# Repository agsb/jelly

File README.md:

-- THIS FILE IS A STUB ---

_01/05/2024 I'm on vacancy for refresh some ideas_

_22/03/2026 Review for make it_

# Jelly revision 2.0

Jelly is a concept, a alternative computer with a diferent paradigm, not for performance but for design.

Jelly is a minimal DIY 8-bit CPU made with CMOS chips, to perform computations using sequential access tapes.

## What is it ?

How make a new cpu without memory address, using only sequential access, for code, data and input/output ?

I want to learn about how old cpus are made by inside and understand about signals, gates, latches, pipelines, etc.

Jelly runs a minimal language, brainfunk, based in brainfuck, a minimal Turing-complete programming language with just eight commands. 

But Jelly includes few new commands to self.

Jelly uses sequential access to two ideal infinite tapes, first for code (aka ONE) and second for data (aka TWO). 

Any device could emulate a tape.

PS: 

The image is from https://en.freejpg.com.ar/free/info/100024149/jelly-fish-blue-water-background-sea-ocean-animal

I know that it will be slow.

Some notes are keeped at [ logbook ](https://github.com/agsb/jelly/blob/main/documents/LogBook.md).

There are a hackday log [ hackio ](https://hackaday.io/project/186689-jelly).

## Ideas

Jelly is not a common cpu.

- There is no general registers, just 3-state latches to keep the data bus safe. 

- There is no arithmetic logical unit (ALU), just a memory with a table of unary "math" results for increment, decrement and copy a byte, and also used to decode opcodes. Could include clear, shift right, shift left, negation.

- There is no comparator, just a flag for when a byte is zero or not.

- Uses Havard architeture, with code and data in diferent tapes.

- There is no memory address, just tapes that moves forward or backward.

- The standart input and output are instant stream devices, not tapes. 

And Jelly executes a esoteric language.

## Brainfunk

Jelly is really, a finite state machine, running by lookup tables and executing a extended version of language brainfuck, called brainfunk, which could have more 8 commands.

Jelly does a classical Read-Eval-Print Loop, or REPL, over bytes received from a code tape. For each byte, use a lookup table to translate into a opcode and execute actions. 

Not all bytes are opcodes and mapped as NOP, do nothing instruction, to catch those and just advance the code tape.

#### Table of OP-CODES
| opcode | ascii | action | code set | name |
| --- | --- | --- | --- | --- |
| 1 | \> | forward a tape one step | brainfuck | forward |
| 2 | \< | backward a tape one step | brainfuck | backward |
| 3 | \+ | increase byte at tape | brainfuck | increase |
| 4 | \- | decrease byte at tape | brainfuck | decrease |
| 5 | \. | output byte from tape | brainfuck | putchar |
| 6 | \, | input byte into tape | brainfuck | getchar |
| 7 | \[ | while loop  | brainfuck | while |
| 8 | \] | until loop  | brainfuck | until |
| 9 | \! | mark end of code | jelly | halt |
| 0 | \= | do nothing | jelly | noop |

- Any other ascii value is just translated as (0x0) noop.
- Opcodes 10, 11, 12, 13, 14, 15 reserved and could change.

## Jelly extensions

Jelly includes: (list can grow)

  - a noop, to do nothing, and moves code tape one step, forward or backward;
  
  - a eof, to end of code and halt, to be a complete Turing Machine;

### Jelly ideas

How the standart devices could be changed ? 

Maybe using the bytes at first two positions of data tape, to select which port to use, as input and output, as like in many microcontrolers ?

The math could include opcodes, for clear, shifts, negation, and reverse a byte.

## About loops

There are some brainfuck computers, but almost with the loop instructions _while_ and _until_ (\[ and \]) replaced by pre-compiled jumps. 

Jelly does not allow pre-compiler tricks, then need a logic to deal with loops.

The _while_ and _until_ loops are like the concepts of any programming language, but used together.

The _while_ ends the loop when the actual data byte is zero, then advances to pass the corresponding _until_. 

The _until_ repeats the loop while the actual data byte is not zero, then must go back after the corresponding _while_.

The loops can be nested, using a counter that increase for begins and decrease for again, finishing the loop when counter is zero. As a 8-bit circuit, the maximum nested loops is 255;

## Circuit Layout

How the Jelly circuit connects is explained in [circuit design](documents/CircuitDesign.md)

### Logic Loops

How loops are implemented in Jelly is explained in [logic loops](documents/LogicLoop.md)

## Main frame

Jelly will be a wirewrap circuit -- work in progress

## Work Bench

Jelly logic circuits needs some tests -- work in progress

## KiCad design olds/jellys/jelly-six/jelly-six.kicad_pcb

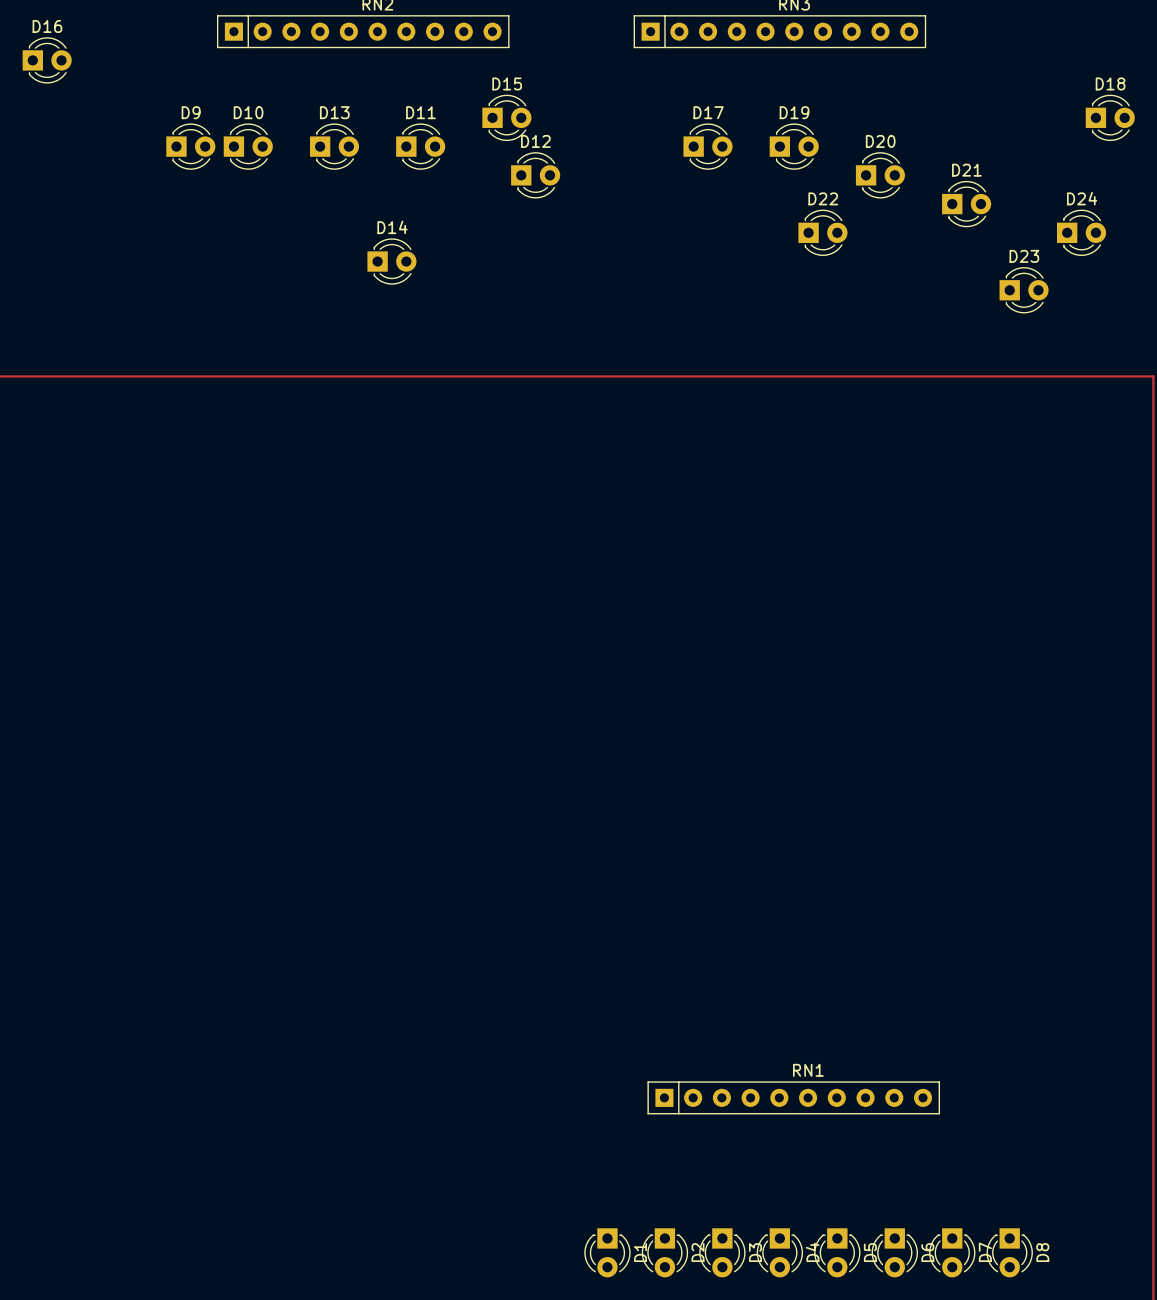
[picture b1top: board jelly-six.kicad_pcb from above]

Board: 2 copper layers, 27 parts (0 on the bottom side), 25 nets, no tracks yet.

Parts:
D1, D2, D3, D4, D5, D6, D7, D8, D9, D10, D11, D12, D13, D14, D15, D16, D17, D18, D19, D20, D21, D22, D23, D24: TSAL4400; LED_D3.0mm_IRBlack
RN1, RN2, RN3: R_Network09_US; R_Array_SIP10

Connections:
GND: RN1.1 (common), RN2.1 (common), RN3.1 (common)
unnamed: D1.1 (K), RN1.2 (R1)
unnamed: D2.1 (K), RN1.3 (R2)
unnamed: D3.1 (K), RN1.4 (R3)
unnamed: D4.1 (K), RN1.5 (R4)
unnamed: D5.1 (K), RN1.6 (R5)
unnamed: D6.1 (K), RN1.7 (R6)
unnamed: D7.1 (K), RN1.8 (R7)
unnamed: D8.1 (K), RN1.9 (R8)
unnamed: D9.1 (K), RN2.2 (R1)
unnamed: D10.1 (K), RN2.3 (R2)
unnamed: D11.1 (K), RN2.4 (R3)
unnamed: D12.1 (K), RN2.5 (R4)
unnamed: D13.1 (K), RN2.6 (R5)
unnamed: D14.1 (K), RN2.7 (R6)
unnamed: D15.1 (K), RN2.8 (R7)
unnamed: D16.1 (K), RN2.9 (R8)
unnamed: D17.1 (K), RN3.2 (R1)
unnamed: D18.1 (K), RN3.3 (R2)
unnamed: D19.1 (K), RN3.4 (R3)
unnamed: D20.1 (K), RN3.5 (R4)
unnamed: D21.1 (K), RN3.6 (R5)
unnamed: D22.1 (K), RN3.7 (R6)
unnamed: D23.1 (K), RN3.8 (R7)
unnamed: D24.1 (K), RN3.9 (R8)

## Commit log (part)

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2022-08-01 add circuits
2022-08-01 small pngs
2022-08-02 more circuits basic
2022-08-12 eeprom math program added
2022-08-17 start of a simulator
2022-08-22 more test dig circuits
2022-08-28 Jelly Blues
2022-08-30 new circuits
2022-08-31 more circuits
2022-09-12 new digital files
2022-09-12 changes in opcode gate logic
2022-09-15 minimal jelly version zero six
2022-09-15 update circuits six
2022-10-05 update digital files
2023-02-03 update dirs
2023-02-03 small texts updates
2023-06-20 glue loop circuit test
2023-06-26 page logics
2023-07-02 jelly digital seven
2023-07-03 update circuits
2023-07-04 new circuit
2023-07-07 update design
2023-07-09 update circuits kicad
2023-07-14 update tests
2023-07-15 jmpjelly emulate
2023-07-19 updates and jmpjelly ok
2023-07-20 new version
2023-07-25 eeprom contents update
2023-07-26 rom checks
2023-07-26 update roms
2023-07-26 update signals notation
2023-08-01 update rom jelly
2023-08-02 updates rom
2023-08-08 update eeproms
2023-08-08 update rom
2023-08-08 Update CircuitDesign.md
    tests of connector design
2023-08-14 make pieces of lucas.bf
2023-08-23 add diylc squema
2023-08-23 adds diylc squemas for wire wrap
2023-08-26 Create WireWrapMap
2023-08-26 Update WireWrapMap
2023-08-26 Rename WireWrapMap to WireWrapMap.md
2023-08-26 wirewrap lists
2023-08-27 wirewrap maps
2023-09-06 update 3 eeprom
2023-09-08 Update LogicLoop.md
    some circuit updates
2023-09-12 changed loop terms
2023-10-27 review disclaimer and LICENSE
2023-10-31 update disclaimer
2026-03-22 22/03/2025 extended review for make it
2026-03-22 Review for make it
2026-03-23 review all connectins and functions
2026-03-23 review all connectins and functions II
2026-03-23 review all connectins and functions III
2026-03-24 review all connectins and functions IV
2026-03-25 review and preserve old files
2026-03-25 review of Jelly
2026-03-25 review of Jelly for 2 finite state eeproms and 1 math eeprom
2026-03-26 this
2026-03-26 unstaged
2026-03-26 Create JellyStates
